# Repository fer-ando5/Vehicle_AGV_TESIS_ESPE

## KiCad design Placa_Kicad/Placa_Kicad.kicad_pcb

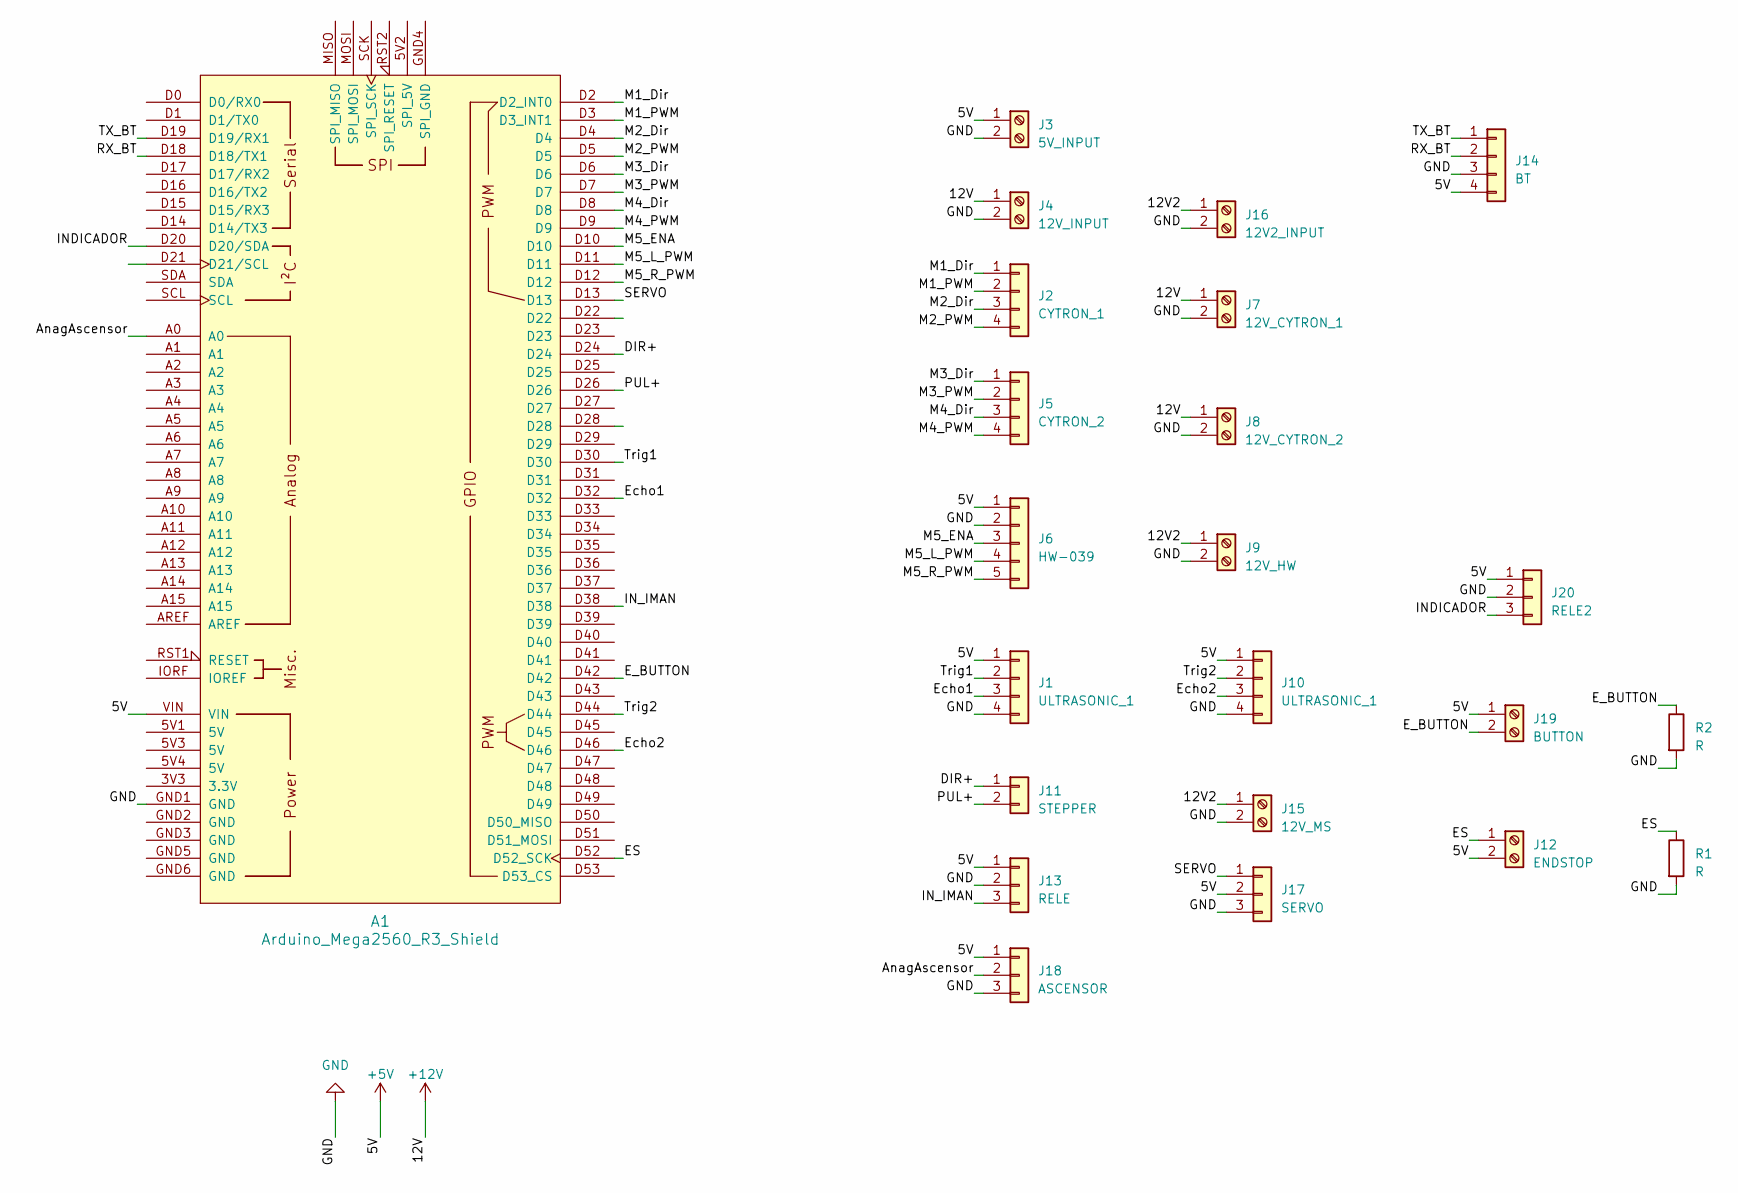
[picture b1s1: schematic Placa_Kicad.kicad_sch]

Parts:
A1: Arduino_Mega2560_R3_Shield
J1, J10: ULTRASONIC_1; JST_EH_B4B-EH-A_1x04_P2.50mm_Vertical
J2: CYTRON_1; JST_EH_B4B-EH-A_1x04_P2.50mm_Vertical
J3: 5V_INPUT; TerminalBlock_bornier-2_P5.08mm
J4: 12V_INPUT; TerminalBlock_bornier-2_P5.08mm
J5: CYTRON_2; JST_EH_B4B-EH-A_1x04_P2.50mm_Vertical
J6: HW-039; JST_EH_B5B-EH-A_1x05_P2.50mm_Vertical
J7: 12V_CYTRON_1; TerminalBlock_4Ucon_1x02_P3.50mm_Horizontal
J8: 12V_CYTRON_2; TerminalBlock_4Ucon_1x02_P3.50mm_Horizontal
J9: 12V_HW; TerminalBlock_4Ucon_1x02_P3.50mm_Horizontal
J11: STEPPER; JST_EH_B2B-EH-A_1x02_P2.50mm_Vertical
J12: ENDSTOP; TerminalBlock_4Ucon_1x02_P3.50mm_Horizontal
J13: RELE; JST_EH_B3B-EH-A_1x03_P2.50mm_Vertical
J14: BT; JST_EH_B4B-EH-A_1x04_P2.50mm_Vertical
J15: 12V_MS; TerminalBlock_4Ucon_1x02_P3.50mm_Horizontal
J16: 12V2_INPUT; TerminalBlock_bornier-2_P5.08mm
J17: SERVO; JST_EH_B3B-EH-A_1x03_P2.50mm_Vertical
J18: ASCENSOR; JST_EH_B3B-EH-A_1x03_P2.50mm_Vertical
J19: BUTTON; TerminalBlock_4Ucon_1x02_P3.50mm_Horizontal
J20: RELE2; JST_EH_B3B-EH-A_1x03_P2.50mm_Vertical
R1, R2: R; R_Axial_DIN0204_L3.6mm_D1.6mm_P7.62mm_Horizontal

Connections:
+5V: A1.VIN, J1.1, J3.1, J6.1, J10.1, J12.2, J13.1, J14.4, J17.2, J18.1, J19.1, J20.1
+12V: J4.1, J7.1, J8.1
/12V2: J9.1, J15.1, J16.1
/AnagAscensor: A1.A0, J18.2
/DIR+: A1.D24, J11.1
/ES: A1.D52 (D52_SCK), J12.1, R1.1
/E_BUTTON: A1.D42, J19.2, R2.1
/Echo1: A1.D32, J1.3
/Echo2: A1.D46, J10.3
/INDICADOR: A1.D20 (D20/SDA), J20.3
/IN_IMAN: A1.D38, J13.3
/M1_Dir: A1.D2 (D2_INT0), J2.1
/M1_PWM: A1.D3 (D3_INT1), J2.2
/M2_Dir: A1.D4, J2.3
/M2_PWM: A1.D5, J2.4
/M3_Dir: A1.D6, J5.1
/M3_PWM: A1.D7, J5.2
/M4_Dir: A1.D8, J5.3
/M4_PWM: A1.D9, J5.4
/M5_ENA: A1.D10, J6.3
/M5_L_PWM: A1.D11, J6.4
/M5_R_PWM: A1.D12, J6.5
/PUL+: A1.D26, J11.2
/RX_BT: A1.D18 (D18/TX1), J14.2
/SERVO: A1.D13, J17.1
/TX_BT: A1.D19 (D19/RX1), J14.1
/Trig1: A1.D30, J1.2
/Trig2: A1.D44, J10.2
GND: A1.GND1 (GND), J1.4, J3.2, J4.2, J6.2, J7.2, J8.2, J9.2, J10.4, J13.2, J14.3, J15.2, J16.2, J17.3, J18.3, J20.2, R1.2, R2.2

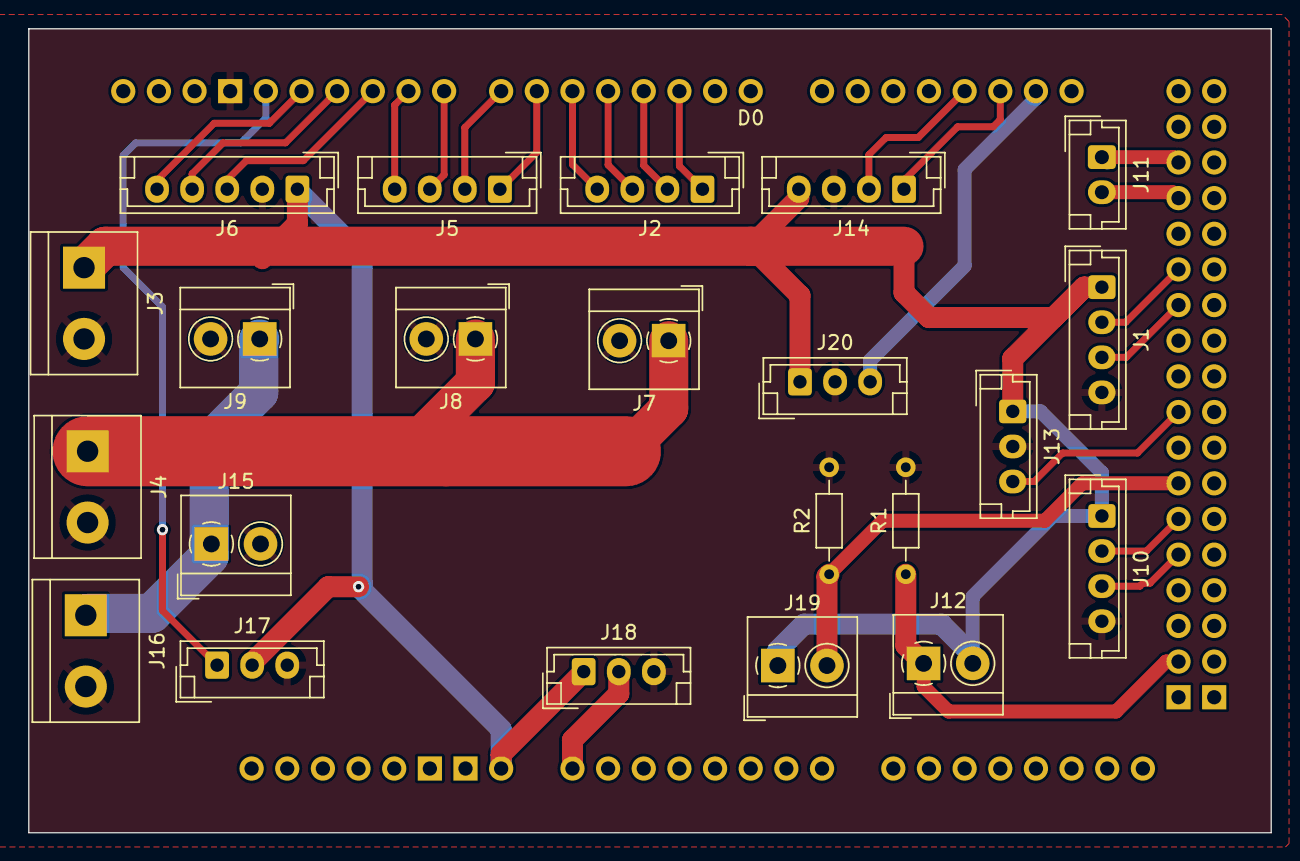
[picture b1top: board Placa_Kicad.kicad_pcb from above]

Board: 2 copper layers, 88.5 x 57.3 mm, 23 parts (0 on the bottom side), 29 nets.

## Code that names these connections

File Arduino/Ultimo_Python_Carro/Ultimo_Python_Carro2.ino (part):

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
//SoftwareSerial BTSerial(19, 18);

// int M1_Dir = 53;
// int M1_Vel = 2;

// int M2_Dir = 51;
// int M2_Vel = 3;

// int M3_Dir = 49;
// int M3_Vel = 4;

// int M4_Dir = 47;
// int M4_Vel = 5;

///////// SERIAL /////////////
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//////////////////////////////

// ========= MOTORES MOVIMIENTO =============//
#define M1_Dir 2
#define M1_Vel 3

#define M2_Dir 4
#define M2_Vel 5

#define M3_Dir 6
#define M3_Vel 7

#define M4_Dir 8
#define M4_Vel 9

String mensaje, m1_vel, m2_vel, m3_vel, m4_vel;
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
#define IMAN 38

#define SERVO_PIN 13
#define ENDSTOP 52

// Define height and maximum height
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// bool EndStop;

//========= ULTRASONIC ========//
#define TRIG1 30
#define ECHO1 32

#define TRIG2 44
#define ECHO2 46

int Distance1;
int Distance2;
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  Serial.begin(115200);
  Serial1.begin(115200);

  pinMode(M1_Dir, OUTPUT);
  pinMode(M1_Vel, OUTPUT);

  pinMode(M2_Dir, OUTPUT);
  pinMode(M2_Vel, OUTPUT);

  pinMode(M3_Dir, OUTPUT);
  pinMode(M3_Vel, OUTPUT);

  pinMode(M4_Dir, OUTPUT);
  pinMode(M4_Vel, OUTPUT);

  //====================
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   // Configurar el pin del endstop como entrada
  pinMode(ENDSTOP, INPUT_PULLUP); // Utiliza un pull-up interno para evitar ruido

    myServo.attach(SERVO_PIN);  // Conecta el servo al pin 9
    setServoAngle(90);  // Establece el ángulo del servo a 0 grados

 
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


    pinMode(TRIG1, OUTPUT);
  pinMode(ECHO1, INPUT);
  
  // Inicializar pines del segundo sensor ultrasónico
  pinMode(TRIG2, OUTPUT);
  pinMode(ECHO2, INPUT);


} 
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
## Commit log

2024-05-08 new file: Aruco_Medicion_Distancia.py new file: GUIA DE COMO SERA TESIS.txt new file: IdentificadorIdAruco.py new file: Tesis version (3).py new file: Tesis_Funciones_Version.py new file: Tesis_QR.py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
2024-05-08 feat: update Aruco_Medicion_Distancia.py
2024-05-08 feat: update Tesis version (3).py feat: update Tesis_Funciones_Version.py
2024-05-08 renamed: Aruco_Medicion_Distancia.py -> Python/Aruco_Medicion_Distancia.py renamed: GUIA DE COMO SERA TESIS.txt -> Python/GUIA DE COMO SERA TESIS.txt renamed: IdentificadorIdAruco.py -> Python/Identi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
2024-05-09 new file: Arduino/EspRobot83/EspRobot83.ino new file: Arduino/Espmesas84/Espmesas84.ino new file: Arduino/Ultimo_Python_Carro/Ultimo_Python_Carro.ino new file: Arduino/WifiCam85/README.md new file: A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
2024-05-26 New: Placa Archivo Base
2024-05-31 Firmware Upgraded - Kicad Base
2024-06-28 modificaciones
2024-06-28 modificacion 1
2024-06-28 modificacion 2
2024-06-28 modificacion 3
2024-06-28 mod 1
2024-06-29 mod6
2024-06-29 mod7
2024-06-30 mod8
2024-06-30 modi1
2024-07-03 Mersh
2024-07-08 Cambios generales, agrego base de datos mosquitto
2024-07-10 Calibracion
2024-07-10 Cal1
2024-07-25 Firmware Completo V1
2024-11-19 cambio
